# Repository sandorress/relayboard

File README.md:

# relayboard
A simple relay board using CORE NRF51822 BLE module

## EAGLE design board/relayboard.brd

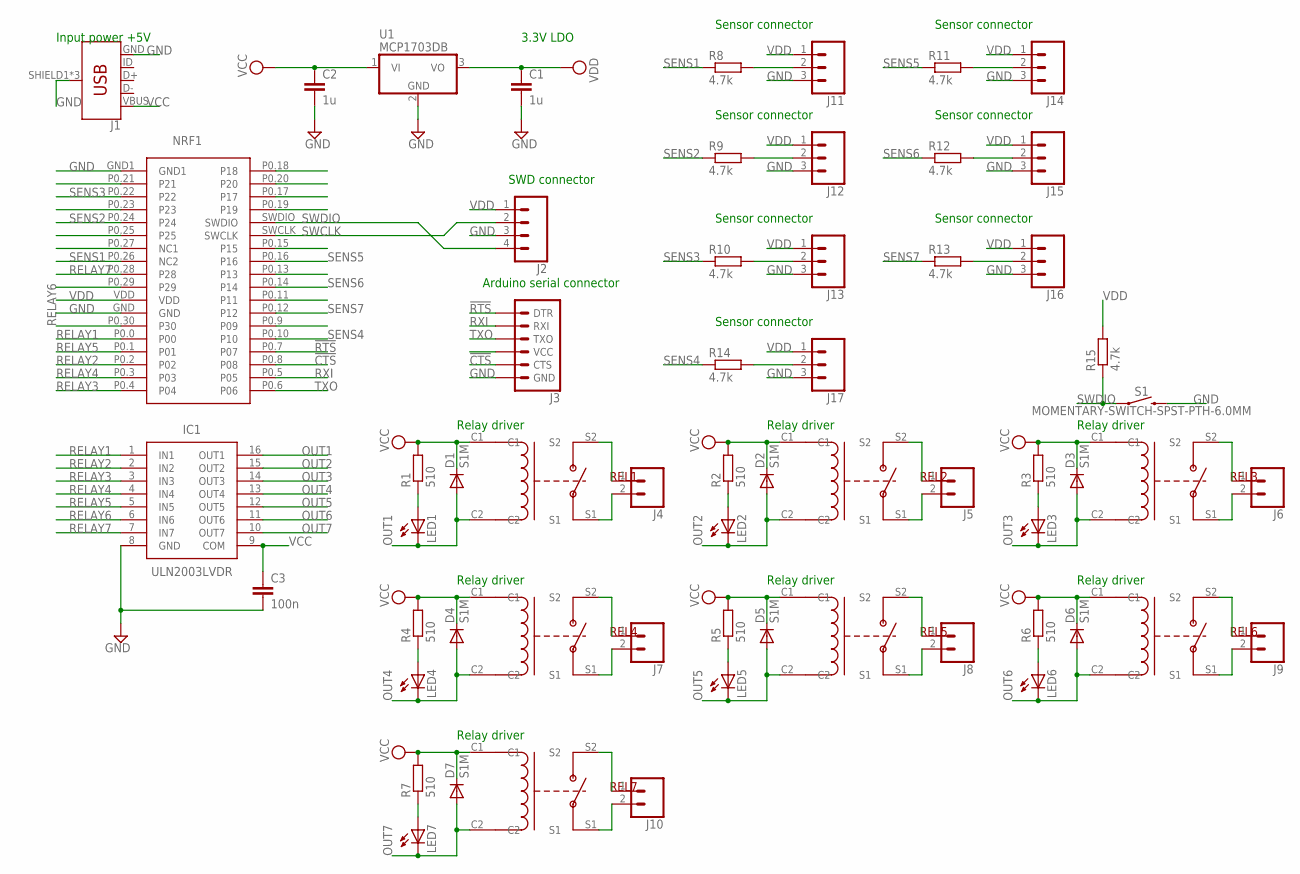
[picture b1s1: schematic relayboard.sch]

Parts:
C1, C2: 1u; C0805
C3: 100n; C0805
D1, D2, D3, D4, D5, D6, D7: S1M; SMA
IC1: ULN2003LVDR; SOIC127P600X175-16N
J1: USB_MICRO-B_FEMALE-SMT; USB-B-MICRO-SMD
J2: CONN_04; 1X04
J3: 6_PIN_SERIAL_TARGET; 1X06
J4, J5, J6, J7, J8, J9, J10: CONN_025MM; SCREWTERMINAL-5MM-2
J11, J12, J13, J14, J15, J16, J17: CONN_03SCREW; SCREWTERMINAL-3.5MM-3
LED1, LED2, LED3, LED4, LED5, LED6, LED7: LEDSML1206; SML1206
NRF1: NRF51822MODULE; NRF
R1, R2, R3, R4, R5, R6, R7: 510; R0603
R8, R9, R10, R11, R12, R13, R14, R15: 4.7k; R0603
REL1, REL2, REL3, REL4, REL5, REL6, REL7: NY5WK
S1: MOMENTARY-SWITCH-SPST-PTH-6.0MM; TACTILE_SWITCH_PTH_6.0MM
U1: MCP1703DB; SOT223

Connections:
!CTS: J3.5 (CTS), NRF1.P0.8 (P08)
!RTS: J3.1 (DTR), NRF1.P0.7 (P07)
GND: C1.2, C2.2, C3.2, IC1.8 (GND), J1.GND, J1.SHIELD1 (SHIELD), J1.SHIELD2 (SHIELD), J1.SHIELD3 (SHIELD), J2.3, J3.6 (GND), J11.3, J12.3, J13.3, J14.3, J15.3, J16.3, J17.3, NRF1.GND, NRF1.GND1, S1.3 (2), U1.2 (GND)
unnamed: LED1.A, R1.1
unnamed: J4.1, REL1.S2
unnamed: J12.2, R9.2
unnamed: J4.2, REL1.S1
unnamed: LED2.A, R2.1
unnamed: J5.1, REL2.S2
unnamed: J5.2, REL2.S1
unnamed: LED3.A, R3.1
unnamed: J6.1, REL3.S2
unnamed: J6.2, REL3.S1
unnamed: LED4.A, R4.1
unnamed: J7.1, REL4.S2
unnamed: J7.2, REL4.S1
unnamed: LED5.A, R5.1
unnamed: J8.1, REL5.S2
unnamed: J8.2, REL5.S1
unnamed: LED6.A, R6.1
unnamed: J9.1, REL6.S2
unnamed: J9.2, REL6.S1
unnamed: LED7.A, R7.1
unnamed: J10.1, REL7.S2
unnamed: J10.2, REL7.S1
unnamed: J11.2, R8.2
unnamed: J13.2, R10.2
unnamed: J14.2, R11.2
unnamed: J15.2, R12.2
unnamed: J16.2, R13.2
unnamed: J17.2, R14.2
OUT1: D1.A, IC1.16 (OUT1), LED1.C, REL1.C2
OUT2: D2.A, IC1.15 (OUT2), LED2.C, REL2.C2
OUT3: D3.A, IC1.14 (OUT3), LED3.C, REL3.C2
OUT4: D4.A, IC1.13 (OUT4), LED4.C, REL4.C2
OUT5: D5.A, IC1.12 (OUT5), LED5.C, REL5.C2
OUT6: D6.A, IC1.11 (OUT6), LED6.C, REL6.C2
OUT7: D7.A, IC1.10 (OUT7), LED7.C, REL7.C2
RELAY1: IC1.1 (IN1), NRF1.P0.0 (P00)
RELAY2: IC1.2 (IN2), NRF1.P0.2 (P02)
RELAY3: IC1.3 (IN3), NRF1.P0.4 (P04)
RELAY4: IC1.4 (IN4), NRF1.P0.3 (P03)
RELAY5: IC1.5 (IN5), NRF1.P0.1 (P01)
RELAY6: IC1.6 (IN6), NRF1.P0.30 (P30)
RELAY7: IC1.7 (IN7), NRF1.P0.28 (P28)
RXI: J3.2 (RXI), NRF1.P0.5 (P05)
SENS1: NRF1.P0.26 (NC2), R8.1
SENS2: NRF1.P0.24 (P24), R9.1
SENS3: NRF1.P0.22 (P22), R10.1
SENS4: NRF1.P0.10 (P10), R14.1
SENS5: NRF1.P0.16 (P16), R11.1
SENS6: NRF1.P0.14 (P14), R12.1
SENS7: NRF1.P0.12 (P12), R13.1
SWCLK: J2.2, NRF1.SWCLK
SWDIO: J2.4, NRF1.SWDIO, R15.1, S1.1
TXO: J3.3 (TXO), NRF1.P0.6 (P06)
VCC: C2.1, C3.1, D1.C, D2.C, D3.C, D4.C, D5.C, D6.C, D7.C, IC1.9 (COM), J1.VBUS, R1.2, R2.2, R3.2, R4.2, R5.2, R6.2, R7.2, REL1.C1, REL2.C1, REL3.C1, REL4.C1, REL5.C1, REL6.C1, REL7.C1, U1.1 (VI)
VDD: C1.1, J2.1, J11.1, J12.1, J13.1, J14.1, J15.1, J16.1, J17.1, NRF1.VDD, R15.2, U1.3 (VO)

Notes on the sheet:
Arduino serial connector
SWD connector
Relay driver
3.3V LDO
Input power +5V
Sensor connector

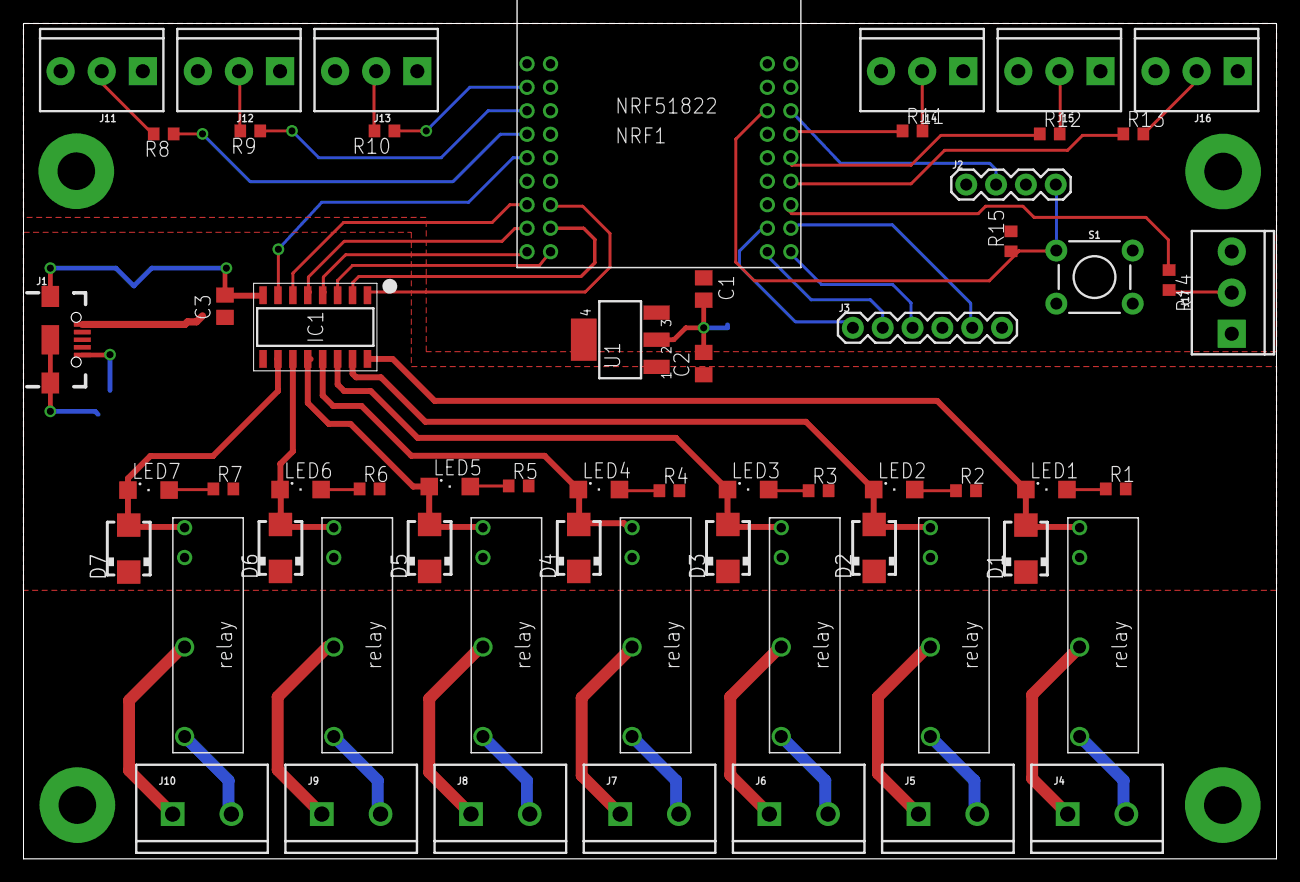
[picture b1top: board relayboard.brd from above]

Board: 2 copper layers, 106.7 x 71.1 mm, 60 parts (0 on the bottom side), 58 nets.

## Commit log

2017-05-02 Initial commit of the board files. LED resistors has been changed to 510 Ohms.

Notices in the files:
parts and their libraries:
SparkFun-Connectors: Licensing: Creative Commons ShareAlike 4.0 International - https://creativecommons.org/licenses/by-sa/4.0
